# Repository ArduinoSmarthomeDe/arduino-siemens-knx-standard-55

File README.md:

# Arduino KNX Siemens 5WG1117 – GIRA Standard 55 mountable

## Description

Arduino Uno clone to wall-mount into *GIRA Standard 55* frames. A *Siemens KNX 5WG1117* bus coupler pcb can be mounted on the backside. There is also a temperature sensor DS18B20 at the front. Needs an ATMega368 chip with Arduino bootloader.

**NOTICE: All brands mentioned are for explanation purposes only. This is NOT an official GIRA or Siemens product and just a pure DIY project.**

*This is just a DIY board, so there is no official KNX stack to configure via the ETS software.*

## Preview

## Parts

| Item      | Part                    | Link  |
| --------- |:-----------------------:| ----- |
| KNX BCU   | SIEMENS 5WG1117-2AB12   | https://www.voltus.de/?cl=details&anid=6d587e3f46216269029d510de0d89711 |

## Layout & Production 

You can find all the open data here as a [KiCad](http://kicad.github.io) project. You can find all the necessary dependencies such as footprints or libraries in the folder **KiCad Symbols & Footprints**.

The *Gerber files* for the production of the board can be found here under **releases**.

## License

The MIT License (MIT)

Copyright (c) 2019 André Husken hello@arduino-smarthome.de

Permission is hereby granted, free of charge, to any person obtaining a copy of this software and associated documentation files (the "Software"), to deal in the Software without restriction, including without limitation the rights to use, copy, modify, merge, publish, distribute, sublicense, and/or sell copies of the Software, and to permit persons to whom the Software is furnished to do so, subject to the following conditions:

The above copyright notice and this permission notice shall be included in all copies or substantial portions of the Software.

THE SOFTWARE IS PROVIDED "AS IS", WITHOUT WARRANTY OF ANY KIND, EXPRESS OR IMPLIED, INCLUDING BUT NOT LIMITED TO THE WARRANTIES OF MERCHANTABILITY, FITNESS FOR A PARTICULAR PURPOSE AND NONINFRINGEMENT. IN NO EVENT SHALL THE AUTHORS OR COPYRIGHT HOLDERS BE LIABLE FOR ANY CLAIM, DAMAGES OR OTHER LIABILITY, WHETHER IN AN ACTION OF CONTRACT, TORT OR OTHERWISE, ARISING FROM, OUT OF OR IN CONNECTION WITH THE SOFTWARE OR THE USE OR OTHER DEALINGS IN THE SOFTWARE.

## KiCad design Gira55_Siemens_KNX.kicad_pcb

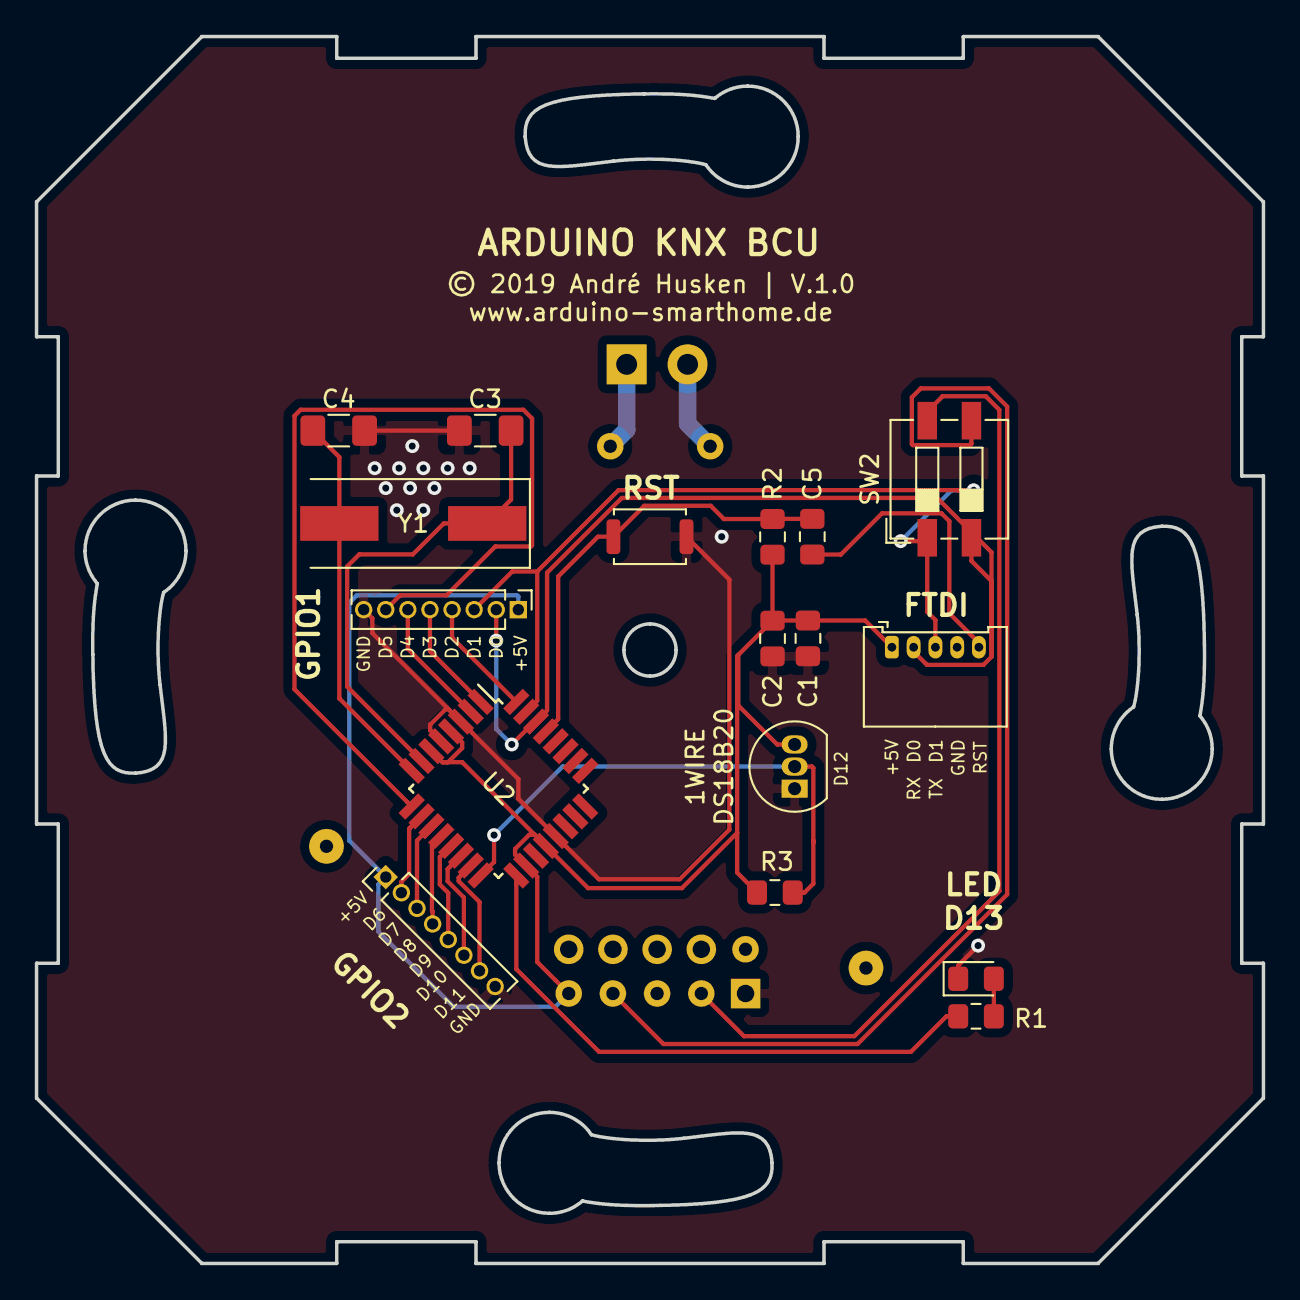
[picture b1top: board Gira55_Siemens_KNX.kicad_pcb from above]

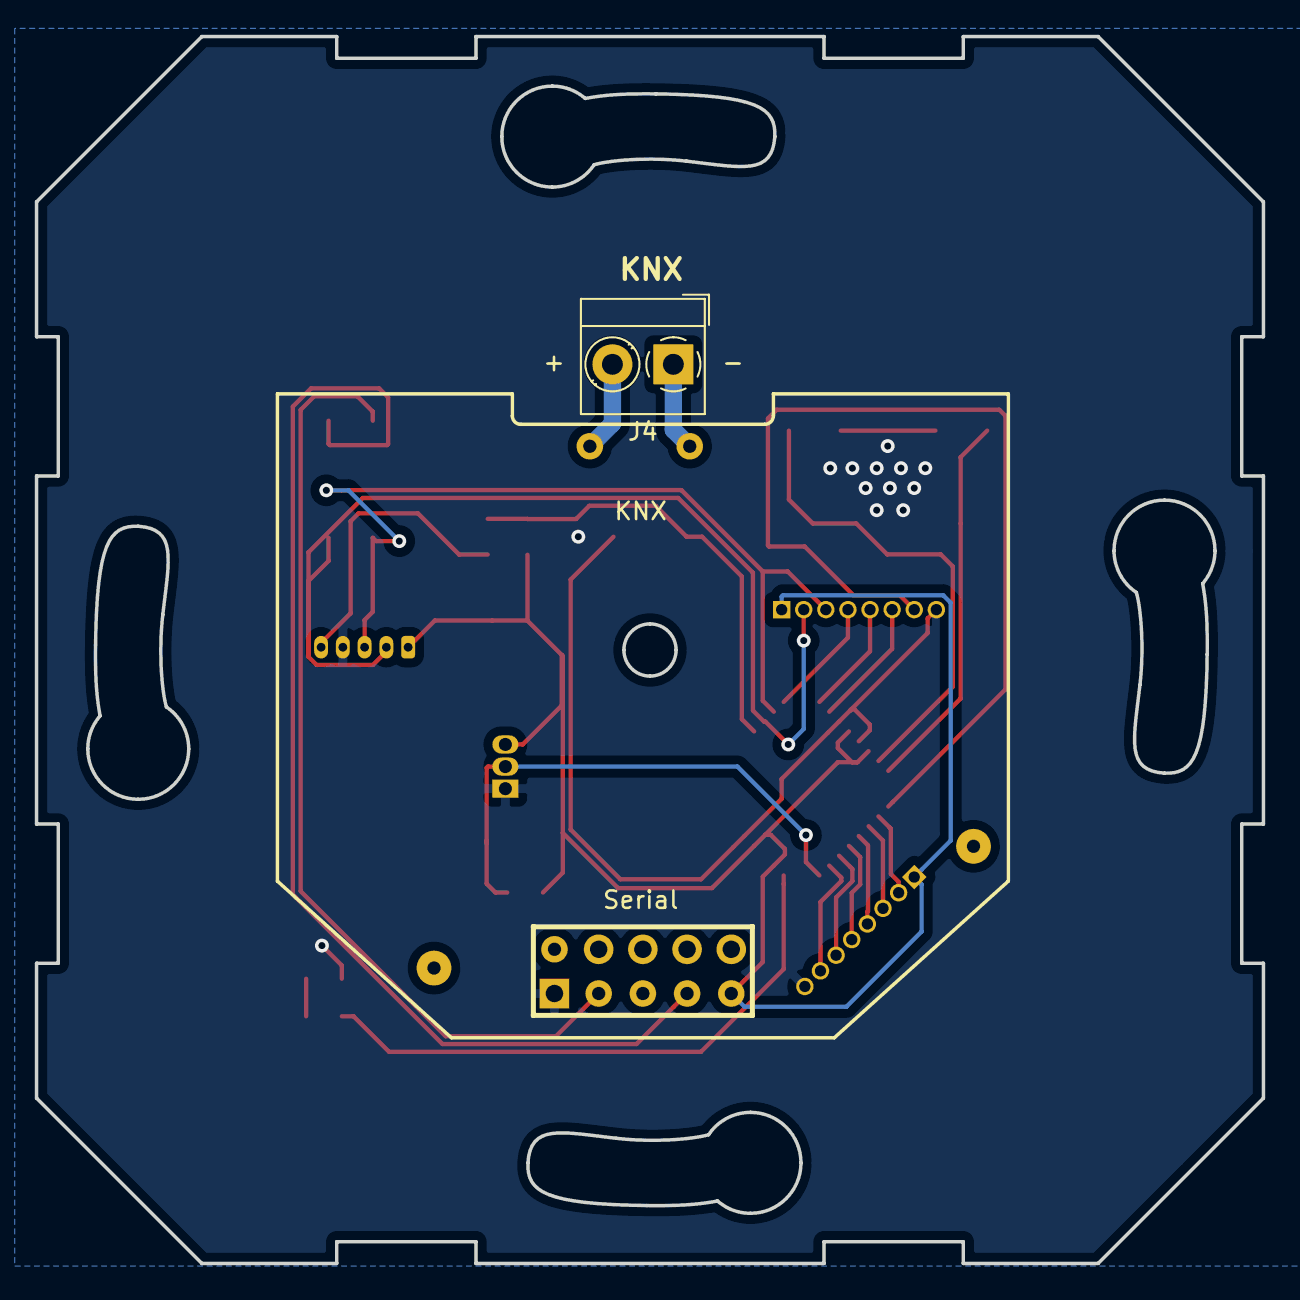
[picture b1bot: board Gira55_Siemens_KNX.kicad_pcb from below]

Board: 2 copper layers, 70.5 x 70.5 mm, 19 parts (2 on the bottom side), 25 nets.

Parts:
C1, C2, C5: 0.1uF; C_0805_2012Metric_Pad1.15x1.40mm_HandSolder
C3, C4: 22pF; C_1206_3216Metric_Pad1.42x1.75mm_HandSolder
D1: LED; LED_0805_2012Metric_Pad1.15x1.40mm_HandSolder
J1: Conn_01x05_Female; Molex_PicoBlade_53048-0510_1x05_P1.25mm_Horizontal
J2, J3: Conn_01x08_Female; PinHeader_1x08_P1.27mm_Vertical
J4: Conn_01x02_Female; TerminalBlock_MetzConnect_Type059_RT06302HBWC_1x02_P3.50mm_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
R1: R; R_0805_2012Metric_Pad1.15x1.40mm_HandSolder
R2: 10K; R_0805_2012Metric_Pad1.15x1.40mm_HandSolder
R3: 4.7K; R_0805_2012Metric_Pad1.15x1.40mm_HandSolder
SW1: SW_Push; SW_Push_SPST_NO_Alps_SKRK
SW2: SW_DIP_x02; SW_DIP_SPSTx02_Slide_6.7x6.64mm_W6.73mm_P2.54mm_LowProfile_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
U1: Siemens_5WG1117
U2: ATmega328P-AU; TQFP-32_7x7mm_P0.8mm
U3: DS18B20; TO-92_Inline
Y1: Crystal; Crystal_SMD_HC49-SD

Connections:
+5V: C1.1, C2.1, J1.1, J2.1, J3.1, R2.1, R3.1, U1.5, U2.4, U2.6, U2.18, U2.20, U3.3
D0: J1.2, J3.2, SW2.2, U2.30
D1: J1.3, J3.3, SW2.1, U2.31
D2: J3.4, U2.32
D3: J3.5, U2.1
D4: J3.6, U2.2
D5: J3.7, U2.9
D6: J2.2, U2.10
D7: J2.3, U2.11
D8: J2.4, U2.12
D9: J2.5, U2.13
D10: J2.6, U2.14
D11: J2.7, U2.15
D12: R3.2, U2.16, U3.2
D13: R1.1, U2.17
GND: C1.2, C2.2, C3.1, C4.2, D1.1, J1.4, J2.8, J3.8, SW1.2, U1.1, U2.3, U2.5, U2.21, U3.1
KNX+: J4.2, U1.11
KNX-: J4.1, U1.12
unnamed: C3.2, U2.7, Y1.1
unnamed: C4.1, U2.8, Y1.2
unnamed: C5.2, R2.2, SW1.1, U2.29
unnamed: D1.2, R1.2
unnamed: SW2.3, U1.4
unnamed: SW2.4, U1.2
RST: C5.1, J1.5

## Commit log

2021-09-08 readme, preview
2021-09-08 V.1.0
2021-09-08 readme

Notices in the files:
Gira55_Siemens_KNX.kicad_pcb:
© 2019 André Husken | V.1.0
